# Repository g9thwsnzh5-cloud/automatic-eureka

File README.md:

# ESP32 Wi-Fi FEM board

Открытая плата на ESP32 с внешним ВЧ-фронтендом (усилитель мощности + малошумящий
усилитель + переключатель) по мотивам ESP32-M1 Reach Out, но на доступных деталях из
каталога LCSC, под сборку на JLCPCB и в рамках лимита 100 мВт.

```
hardware/kicad/       KiCad 7 проект (схема, плата, библиотека)
hardware/kicad/tools/ генераторы: design.py (детали и цепи), gen_sch.py, gen_pcb.py, route.py
firmware/             ESP-IDF: компонент управления усилителем + тест дальности
docs/design.md        описание конструкции и отличия от оригинала (rev A)
docs/design_pico.md   rev B: ESP32-PICO-D4 без пигтейла
docs/design_1w.md     вариант 1 Вт (QPF4219) — схема и BOM, без разводки
docs/ordering.md      как заказать на JLCPCB, что докупить, первое включение
docs/review*.md       результаты ревью субагентами и статус правок
```

Три варианта в одном генераторе (переменная `DESIGN`):

| Вариант | Файл | Мощность | Состояние |
|---|---|---|---|
| rev A | `design.py` → `esp32_fem.*` | 100 мВт (RFX2401C), модуль WROOM-32U + пигтейл | разведена, DRC 0, файлы в `build/fab/` |
| rev B | `design_pico.py` → `esp32_fem_pico.*` | 100 мВт, голый ESP32-PICO-D4, без пигтейла | разведена, DRC 0, файлы в `build/fab_pico/` |
| 1 Вт | `design_1w.py` → `esp32_fem_1w.*` | 1 Вт (QPF4219 + RFSW8009), только для лаборатории | схема и BOM проверены, разводки нет |

## Ключевые параметры

| | |
|---|---|
| Модуль | ESP32-WROOM-32U-N4 (внешняя антенна через U.FL) |
| Фронтенд | RFX2401C: PA до +20 дБм, LNA 12 дБ, 3,3 В |
| Управление | GPIO23 = TXEN, GPIO18 = RXEN через `esp_wifi_set_ant_gpio()` |
| Плата | 4 слоя, 64 × 52 мм, стек JLC04161H-7628, микрополосок 0,38 мм |
| Интерфейс | USB-C, CH340C, автосброс DTR/RTS, кнопки RESET/BOOT |
| Антенна | SMA/RP-SMA edge-mount |

## Как пересобрать файлы

```bash
cd hardware/kicad
python3 tools/gen_sch.py                                  # схема из design.py
kicad-cli sch export netlist --format kicadsexpr -o build/esp32_fem.net esp32_fem.kicad_sch
python3 tools/gen_pcb.py                                  # плата: размещение, ВЧ-дорожки, полигоны
# автотрассировка остальных цепей (freerouting), затем:
python3 tools/route.py import                             # импорт .ses, заливка полигонов
python3 tools/route.py drc                                # отчёт DRC в build/drc.rpt
python3 tools/route.py fab                                # Gerber, сверловка, BOM и CPL для JLCPCB
```

Для rev B — то же с `DESIGN=design_pico` перед каждой командой (файлы `esp32_fem_pico.*`,
freerouting запускать с `-inc RF,SKIP`: ВЧ и земля роутеру закрыты; см. `build/run_pico.sh`).
Для 1 Вт — `DESIGN=design_1w` (только схема).

Плату можно открыть и править в KiCad 7/8 как обычный проект.

## Прошивка

```bash
cd firmware
idf.py set-target esp32
idf.py menuconfig      # FEM board -> SSID, пароль, мощность
idf.py build flash monitor
```

Компонент `fem_rfx2401` можно перенести в любой другой проект (например в esp32_nat_router):
вызвать `fem_rfx2401_init()` после `esp_wifi_init()` и `fem_rfx2401_set_tx_power(32)` после
`esp_wifi_start()`.

## Статус

Rev A и rev B разведены и проверены DRC, ни одна пока не изготавливалась. Перед заказом см.
`docs/ordering.md` и итоги ревью в `docs/review.md`, `docs/review_revB.md`.

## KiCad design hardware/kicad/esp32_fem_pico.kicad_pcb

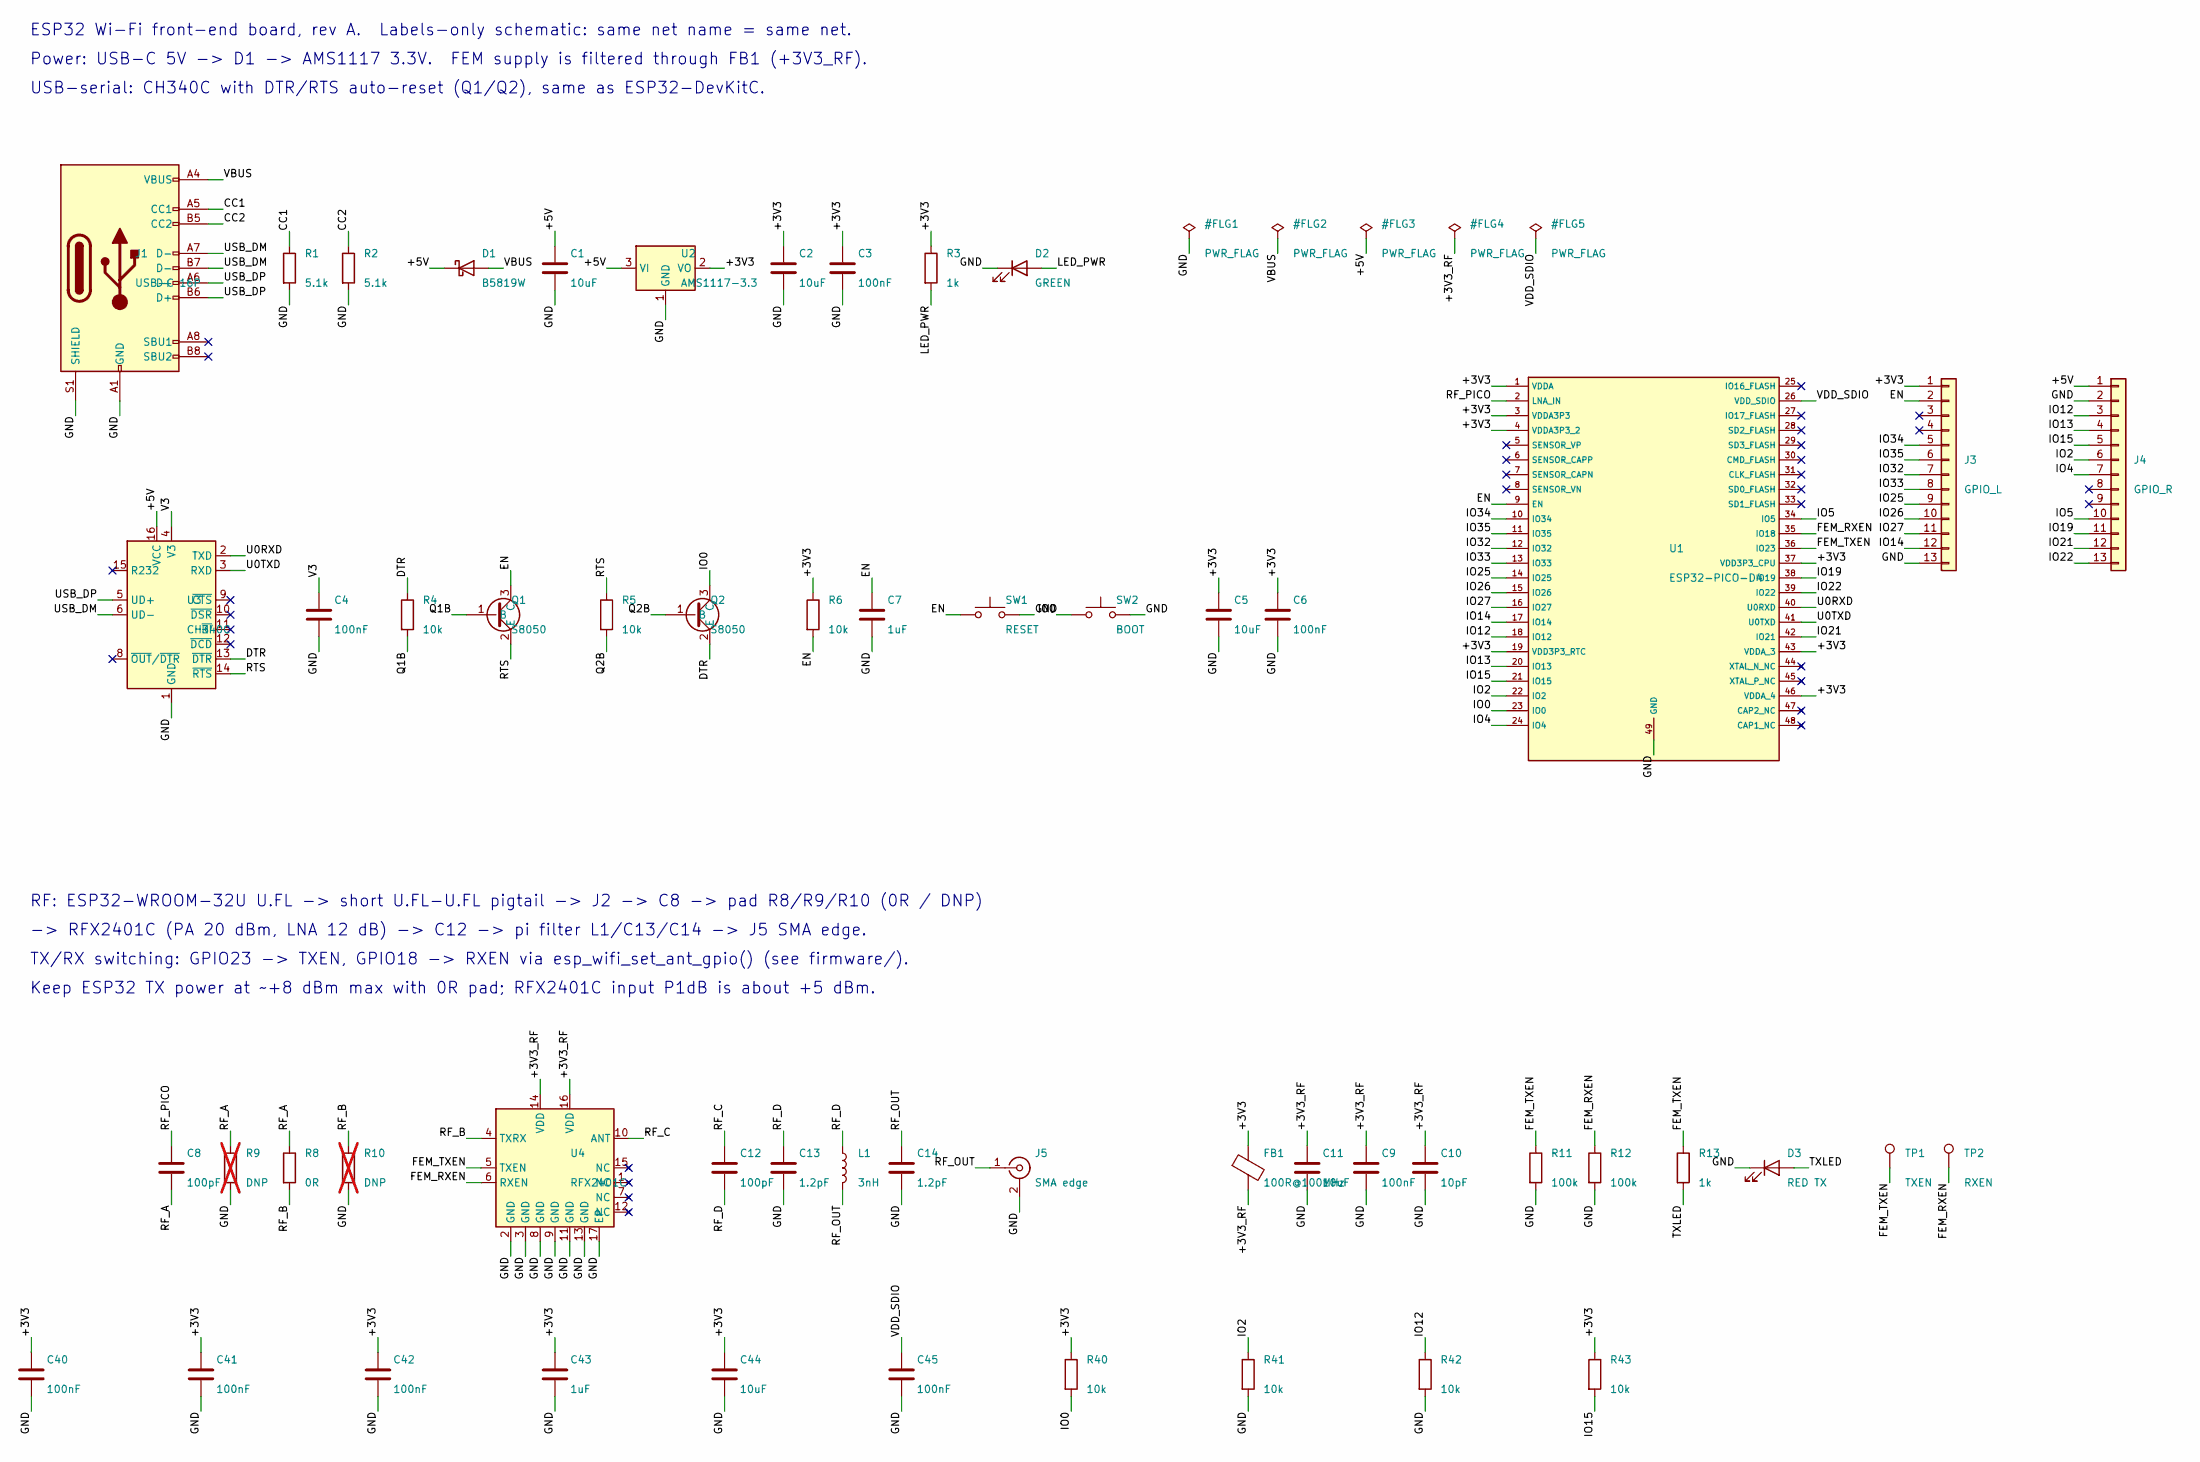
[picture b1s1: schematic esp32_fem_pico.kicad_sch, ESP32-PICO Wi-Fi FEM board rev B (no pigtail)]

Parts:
C1, C2, C5, C11, C44: 10uF; C_0603_1608Metric; LCSC C19702
C3, C4, C6, C9, C40, C41, C42, C45: 100nF; C_0402_1005Metric; LCSC C1525
C7, C43: 1uF; C_0402_1005Metric; LCSC C52923
C8, C12: 100pF; C_0402_1005Metric; LCSC C1546
C10: 10pF; C_0402_1005Metric; LCSC C32949
C13, C14: 1.2pF; C_0402_1005Metric; LCSC C327292
D1: B5819W; D_SOD-123; LCSC C8598
D2: GREEN; LED_0603_1608Metric; LCSC C72043
D3: RED TX; LED_0603_1608Metric; LCSC C2286
FB1: 100R@100MHz; L_0805_2012Metric; LCSC C1015
J1: USB-C 16P; USB_C_Receptacle_HRO_TYPE-C-31-M-12; LCSC C165948
J3: GPIO_L; PinHeader_1x13_P2.54mm_Vertical; JLC_ASSEMBLE no
J4: GPIO_R; PinHeader_1x13_P2.54mm_Vertical; JLC_ASSEMBLE no
J5: SMA edge; SMA_Amphenol_132289_EdgeMount; JLC_ASSEMBLE no
L1: 3nH; L_0402_1005Metric; LCSC C269824
Q1, Q2: S8050; SOT-23; LCSC C2150
R1, R2: 5.1k; R_0402_1005Metric; LCSC C25905
R3, R13: 1k; R_0402_1005Metric; LCSC C11702
R4, R5, R6, R40, R41, R42, R43: 10k; R_0402_1005Metric; LCSC C25744
R8: 0R; R_0402_1005Metric; LCSC C17168
R9, R10: DNP; R_0402_1005Metric; JLC_ASSEMBLE yes; not fitted
R11, R12: 100k; R_0402_1005Metric; LCSC C25741
SW1: RESET; SW_PUSH_6mm; JLC_ASSEMBLE no
SW2: BOOT; SW_PUSH_6mm; JLC_ASSEMBLE no
TP1: TXEN; TestPoint_Pad_1.0x1.0mm; JLC_ASSEMBLE no
TP2: RXEN; TestPoint_Pad_1.0x1.0mm; JLC_ASSEMBLE no
U1: ESP32-PICO-D4; LCSC C193707
U2: AMS1117-3.3; SOT-223-3_TabPin2; LCSC C6186
U3: CH340C; SOIC-16_3.9x9.9mm_P1.27mm; LCSC C84681
U4: RFX2401C; QFN-16-1EP_3x3mm_P0.5mm_EP1.7x1.7mm_ThermalVias; LCSC C19213

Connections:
+3V3: C2.1, C3.1, C5.1, C6.1, C40.1, C41.1, C42.1, C43.1, C44.1, FB1.1, J3.1, R3.1, R6.1, R40.1, R43.1, U1.1 (VDDA), U1.3 (VDDA3P3), U1.4 (VDDA3P3_2), U1.19 (VDD3P3_RTC), U1.37 (VDD3P3_CPU), U1.43 (VDDA_3), U1.46 (VDDA_4), U2.2 (VO)
+3V3_RF: C9.1, C10.1, C11.1, FB1.2, U4.14 (VDD), U4.16 (VDD)
+5V: C1.1, D1.1 (K), J4.1, U2.3 (VI), U3.16 (VCC)
CC1: J1.A5 (CC1), R1.1
CC2: J1.B5 (CC2), R2.1
DTR: Q2.2 (E), R4.1, U3.13 (~DTR)
EN: C7.1, J3.2, Q1.3 (C), R6.2, SW1.1, U1.9 (EN)
FEM_RXEN: R12.1, TP2.1, U1.35 (IO18), U4.6 (RXEN)
FEM_TXEN: R11.1, R13.1, TP1.1, U1.36 (IO23), U4.5 (TXEN)
GND: C1.2, C2.2, C3.2, C4.2, C5.2, C6.2, C7.2, C9.2, C10.2, C11.2, C13.2, C14.2, C40.2, C41.2, C42.2, C43.2, C44.2, C45.2, D2.1 (K), D3.1 (K), J1.A1 (GND), J1.A12 (GND), J1.B1 (GND), J1.B12 (GND), J1.S1 (SHIELD), J3.13, J4.2, J5.2 (Ext), R1.2, R2.2, R9.2, R10.2, R11.2, R12.2, R41.2, R42.2, SW1.2, SW2.2, U1.49 (GND), U2.1 (GND), U3.1 (GND), U4.2 (GND), U4.3 (GND), U4.8 (GND), U4.9 (GND), U4.11 (GND), U4.13 (GND), U4.17 (EP)
IO0: Q2.3 (C), R40.2, SW2.1, U1.23 (IO0)
IO2: J4.6, R41.1, U1.22 (IO2)
IO4: J4.7, U1.24 (IO4)
IO5: J4.10, U1.34 (IO5)
IO12: J4.3, R42.1, U1.18 (IO12)
IO13: J4.4, U1.20 (IO13)
IO14: J3.12, U1.17 (IO14)
IO15: J4.5, R43.2, U1.21 (IO15)
IO19: J4.11, U1.38 (IO19)
IO21: J4.12, U1.42 (IO21)
IO22: J4.13, U1.39 (IO22)
IO25: J3.9, U1.14 (IO25)
IO26: J3.10, U1.15 (IO26)
IO27: J3.11, U1.16 (IO27)
IO32: J3.7, U1.12 (IO32)
IO33: J3.8, U1.13 (IO33)
IO34: J3.5, U1.10 (IO34)
IO35: J3.6, U1.11 (IO35)
LED_PWR: D2.2 (A), R3.2
Q1B: Q1.1 (B), R4.2
Q2B: Q2.1 (B), R5.2
RF_A: C8.2, R8.1, R9.1
RF_B: R8.2, R10.1, U4.4 (TXRX)
RF_C: C12.1, U4.10 (ANT)
RF_D: C12.2, C13.1, L1.1
RF_OUT: C14.1, J5.1 (In), L1.2
RF_PICO: C8.1, U1.2 (LNA_IN)
RTS: Q1.2 (E), R5.1, U3.14 (~RTS)
TXLED: D3.2 (A), R13.2
U0RXD: U1.40 (U0RXD), U3.2 (TXD)
U0TXD: U1.41 (U0TXD), U3.3 (RXD)
USB_DM: J1.A7 (D-), J1.B7 (D-), U3.6 (UD-)
USB_DP: J1.A6 (D+), J1.B6 (D+), U3.5 (UD+)
V3: C4.1, U3.4 (V3)
VBUS: D1.2 (A), J1.A4 (VBUS), J1.A9 (VBUS), J1.B4 (VBUS), J1.B9 (VBUS)
VDD_SDIO: C45.1, U1.26 (VDD_SDIO)

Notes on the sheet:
ESP32 Wi-Fi front-end board, rev A. Labels-only schematic: same net name = same net.
Power: USB-C 5V -> D1 -> AMS1117 3.3V. FEM supply is filtered through FB1 (+3V3_RF).
USB-serial: CH340C with DTR/RTS auto-reset (Q1/Q2), same as ESP32-DevKitC.
RF: ESP32-WROOM-32U U.FL -> short U.FL-U.FL pigtail -> J2 -> C8 -> pad R8/R9/R10 (0R / DNP)
-> RFX2401C (PA 20 dBm, LNA 12 dB) -> C12 -> pi filter L1/C13/C14 -> J5 SMA edge.
TX/RX switching: GPIO23 -> TXEN, GPIO18 -> RXEN via esp_wifi_set_ant_gpio() (see firmware/).
Keep ESP32 TX power at ~+8 dBm max with 0R pad; RFX2401C input P1dB is about +5 dBm.

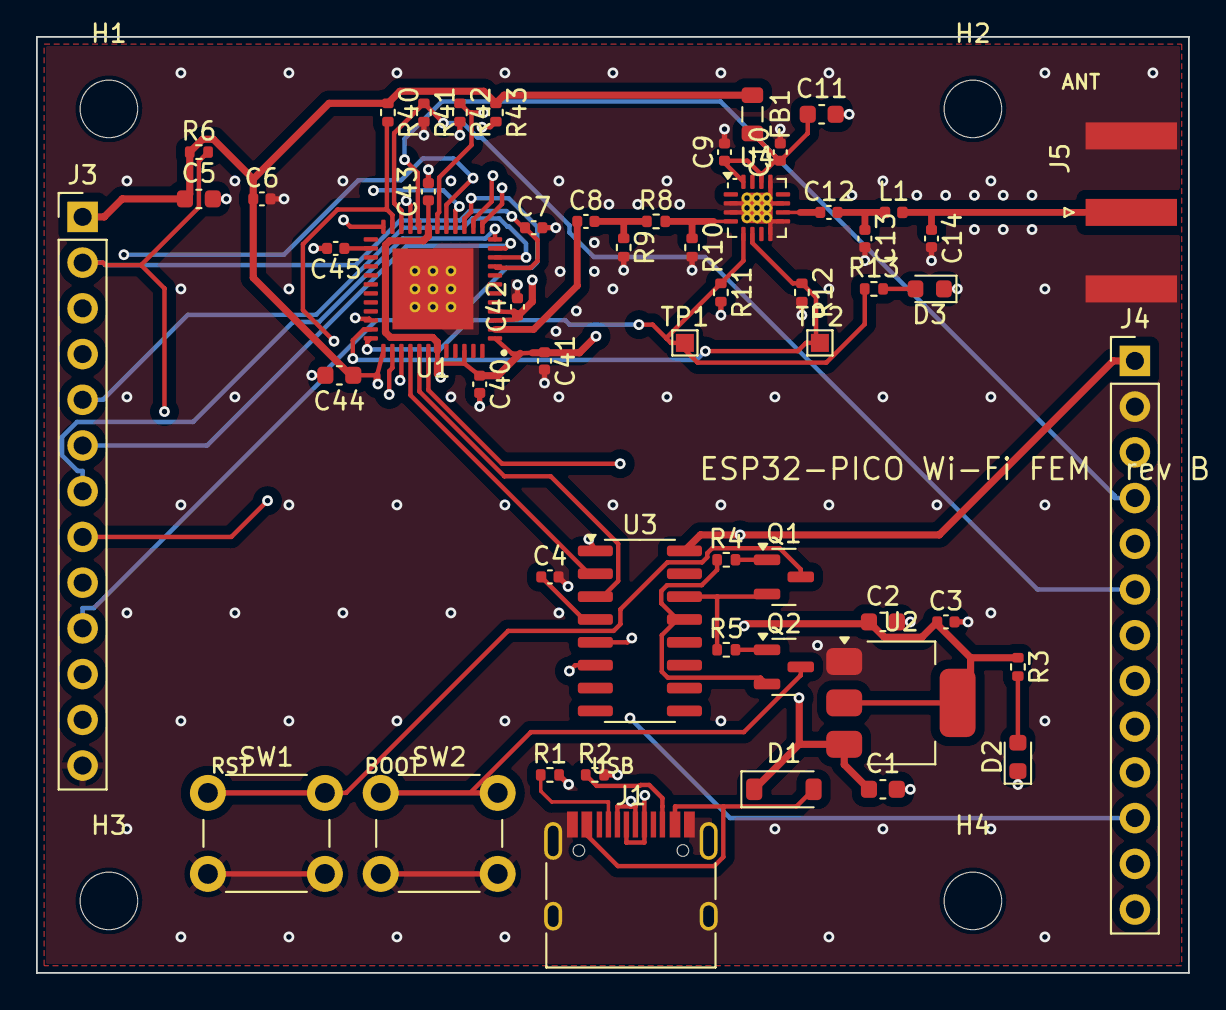
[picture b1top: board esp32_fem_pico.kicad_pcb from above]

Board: 4 copper layers, 64.0 x 52.0 mm, 59 parts (0 on the bottom side), 46 nets.

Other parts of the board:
H1, H2, H3, H4: M3; MountingHole_3.2mm_M3

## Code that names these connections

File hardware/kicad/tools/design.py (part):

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    dict(ref="C3", sym="Device:C", value="100nF", fp=C0402, lcsc="C1525",
         pins={"1": "+3V3", "2": "GND"}),
    dict(ref="R3", sym="Device:R", value="1k", fp=R0402, lcsc="C11702",
         pins={"1": "+3V3", "2": "LED_PWR"}),
    dict(ref="D2", sym="Device:LED", value="GREEN", fp=LED0603, lcsc="C72043",
         pins={"2": "LED_PWR", "1": "GND"}),

    # --- USB to serial and auto-reset -------------------------------------
    dict(ref="U3", sym="Interface_USB:CH340C", value="CH340C", fp=SOIC16, lcsc="C84681",
         pins={"16": "+5V", "1": "GND", "4": "V3", "5": "USB_DP", "6": "USB_DM",
               "2": "U0RXD", "3": "U0TXD", "13": "DTR", "14": "RTS"},
         nc=["8", "9", "10", "11", "12", "15"]),
    dict(ref="C4", sym="Device:C", value="100nF", fp=C0402, lcsc="C1525",
         pins={"1": "V3", "2": "GND"}),
    dict(ref="R4", sym="Device:R", value="10k", fp=R0402, lcsc="C25744",
         pins={"1": "DTR", "2": "Q1B"}),
    dict(ref="Q1", sym="esp32_fem:S8050_SOT23", value="S8050", fp=SOT23, lcsc="C2150",
         pins={"1": "Q1B", "2": "RTS", "3": "EN"}),
    dict(ref="R5", sym="Device:R", value="10k", fp=R0402, lcsc="C25744",
         pins={"1": "RTS", "2": "Q2B"}),
    dict(ref="Q2", sym="esp32_fem:S8050_SOT23", value="S8050", fp=SOT23, lcsc="C2150",
         pins={"1": "Q2B", "2": "DTR", "3": "IO0"}),

    # --- ESP32 module -----------------------------------------------------
    dict(ref="U1", sym="RF_Module:ESP32-WROOM-32U", value="ESP32-WROOM-32U-N4", fp=ESP32U,
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    dict(ref="J2", sym="Connector:Conn_Coaxial", value="U.FL RF_IN", fp=UFL, lcsc="C88374",
         pins={"1": "RF_IN", "2": "GND"}),
    dict(ref="C8", sym="Device:C", value="100pF", fp=C0402, lcsc="C1546",
         pins={"1": "RF_IN", "2": "RF_A"}),
    dict(ref="R9", sym="Device:R", value="DNP", fp=R0402, lcsc="", dnp=True,
         pins={"1": "RF_A", "2": "GND"}),
    dict(ref="R8", sym="Device:R", value="0R", fp=R0402, lcsc="C17168",
         pins={"1": "RF_A", "2": "RF_B"}),
    dict(ref="R10", sym="Device:R", value="DNP", fp=R0402, lcsc="", dnp=True,
         pins={"1": "RF_B", "2": "GND"}),
    dict(ref="U4", sym="esp32_fem:RFX2401C", value="RFX2401C", fp=QFN16, lcsc="C19213",
         pins={"4": "RF_B", "5": "FEM_TXEN", "6": "FEM_RXEN", "10": "RF_C",
               "14": "+3V3_RF", "16": "+3V3_RF",
               "2": "GND", "3": "GND", "8": "GND", "9": "GND", "11": "GND", "13": "GND",
               "17": "GND"},
         nc=["1", "7", "12", "15"]),
    dict(ref="C12", sym="Device:C", value="100pF", fp=C0402, lcsc="C1546",
         pins={"1": "RF_C", "2": "RF_D"}),
    dict(ref="C13", sym="Device:C", value="1.2pF", fp=C0402, lcsc="C327292",
         pins={"1": "RF_D", "2": "GND"}),
    dict(ref="L1", sym="Device:L", value="3nH", fp=L0402, lcsc="C269824",
         pins={"1": "RF_D", "2": "RF_OUT"}),
    dict(ref="C14", sym="Device:C", value="1.2pF", fp=C0402, lcsc="C327292",
         pins={"1": "RF_OUT", "2": "GND"}),
    dict(ref="J5", sym="Connector:Conn_Coaxial", value="SMA edge", fp=SMA, lcsc="", jlc=False,
         pins={"1": "RF_OUT", "2": "GND"}),

    # --- FEM supply and control -------------------------------------------
    dict(ref="FB1", sym="Device:FerriteBead", value="100R@100MHz", fp=L0805, lcsc="C1015",
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    dict(ref="C10", sym="Device:C", value="10pF", fp=C0402, lcsc="C32949",
         pins={"1": "+3V3_RF", "2": "GND"}),
    dict(ref="R11", sym="Device:R", value="100k", fp=R0402, lcsc="C25741",
         pins={"1": "FEM_TXEN", "2": "GND"}),
    dict(ref="R12", sym="Device:R", value="100k", fp=R0402, lcsc="C25741",
         pins={"1": "FEM_RXEN", "2": "GND"}),
    dict(ref="R13", sym="Device:R", value="1k", fp=R0402, lcsc="C11702",
         pins={"1": "FEM_TXEN", "2": "TXLED"}),
    dict(ref="D3", sym="Device:LED", value="RED TX", fp=LED0603, lcsc="C2286",
         pins={"2": "TXLED", "1": "GND"}),
    dict(ref="TP1", sym="Connector:TestPoint", value="TXEN", fp=TP, lcsc="", jlc=False,
         pins={"1": "FEM_TXEN"}),
    dict(ref="TP2", sym="Connector:TestPoint", value="RXEN", fp=TP, lcsc="", jlc=False,
         pins={"1": "FEM_RXEN"}),
]

# Nets that need a PWR_FLAG so ERC sees a driver.
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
